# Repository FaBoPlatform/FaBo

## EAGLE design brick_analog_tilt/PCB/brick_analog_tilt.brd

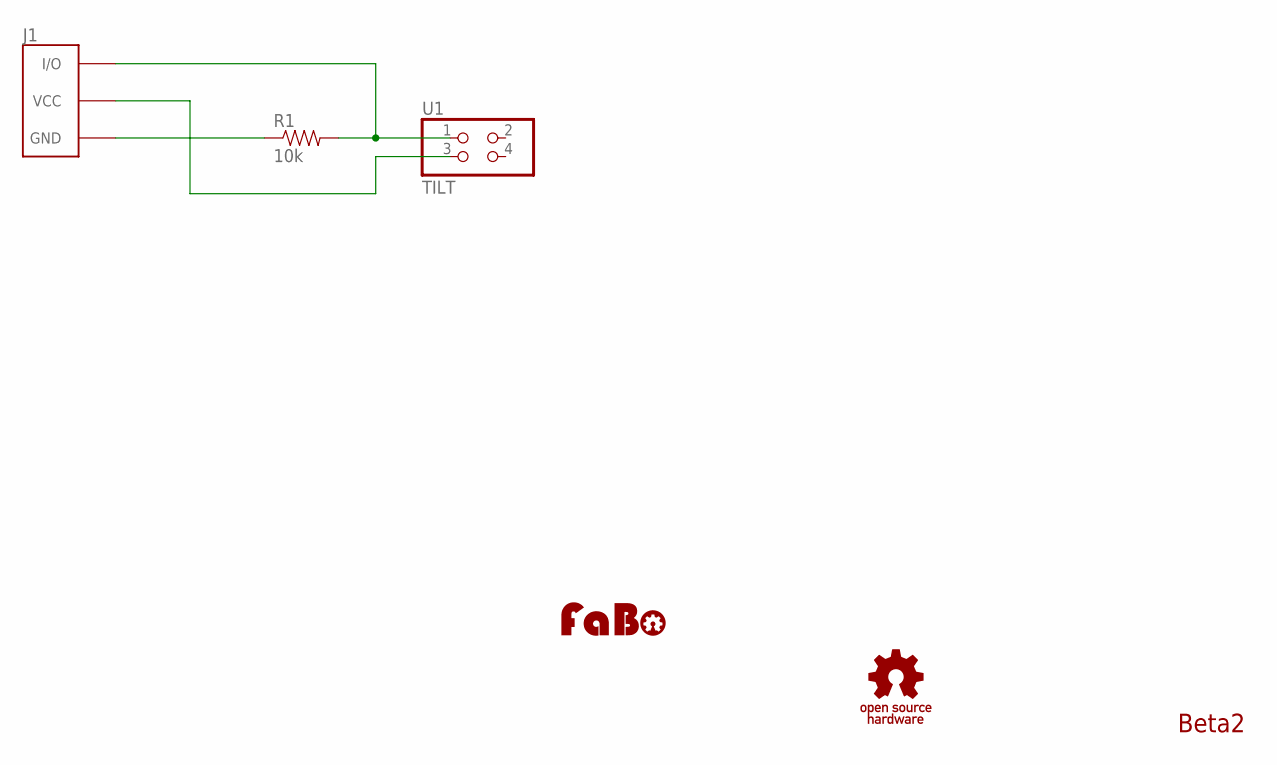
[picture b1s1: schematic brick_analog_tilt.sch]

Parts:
J1: BRICK_3PIN
R1: 10k; RES-AXL-REGULAR
U1: TILT; 2X02
U$2: LOGO_OSHW_T-M; LOGO_OSHW_T_M
U$3: LOGO_FABO-M; LOGO_FABO_M

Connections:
GND: J1.GND, R1.P$1 (1)
unnamed: J1.IN/OUT (I/O), R1.P$2 (2), U1.1
unnamed: J1.VCC, U1.3

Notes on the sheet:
Beta2

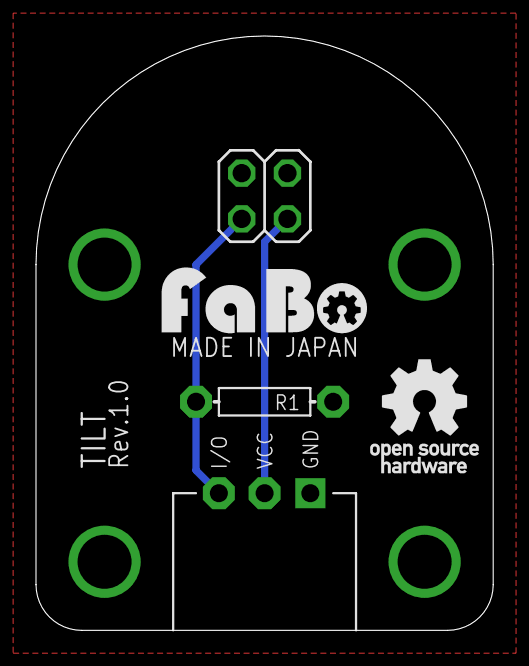
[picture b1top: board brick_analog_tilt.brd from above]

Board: 2 copper layers, 25.4 x 33.0 mm, 5 parts (0 on the bottom side), 3 nets.

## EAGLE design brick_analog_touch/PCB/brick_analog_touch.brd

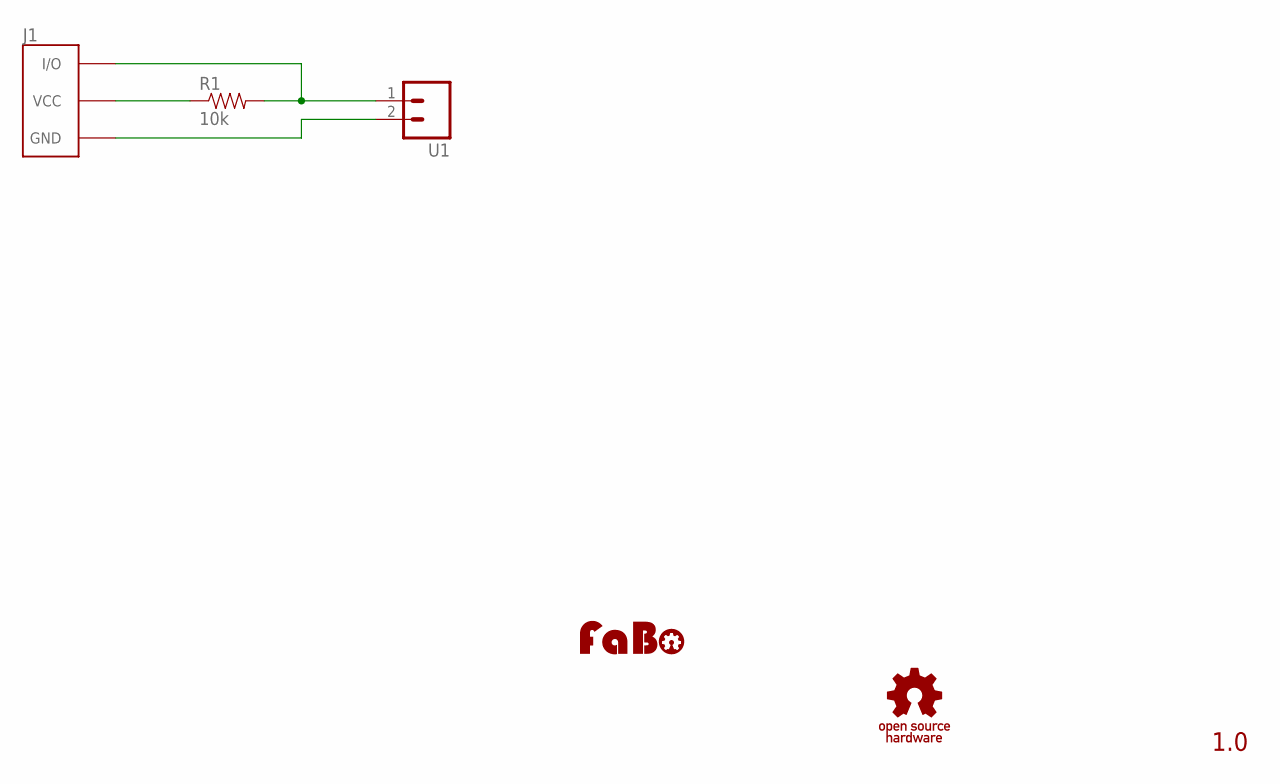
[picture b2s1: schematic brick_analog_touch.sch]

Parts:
J1: BRICK_3PIN_NORMAL; BRICK_3PIN
R1: 10k; RES-AXL-REGULAR
U1: M02LOCK; 1X02_LOCK
U$2: LOGO_OSHW_T-M; LOGO_OSHW_T_M
U$3: LOGO_FABO-M; LOGO_FABO_M

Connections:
GND: J1.GND, U1.2
unnamed: J1.IN/OUT (I/O), R1.P$2 (2), U1.1
unnamed: J1.VCC, R1.P$1 (1)

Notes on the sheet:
1.0

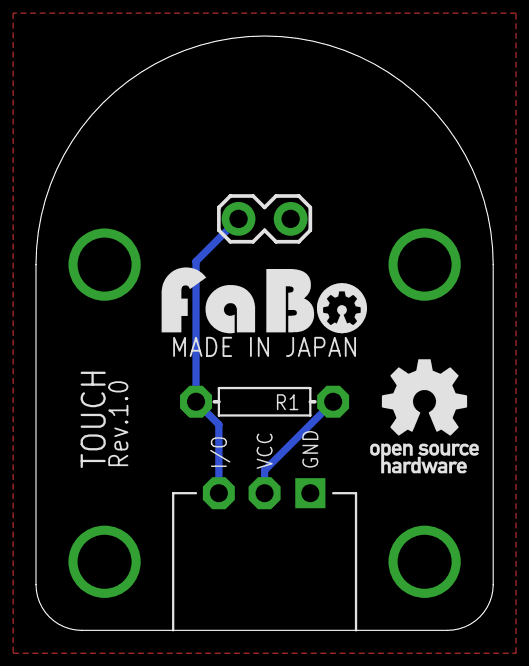
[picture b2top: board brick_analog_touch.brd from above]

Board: 2 copper layers, 25.4 x 33.0 mm, 5 parts (0 on the bottom side), 3 nets.

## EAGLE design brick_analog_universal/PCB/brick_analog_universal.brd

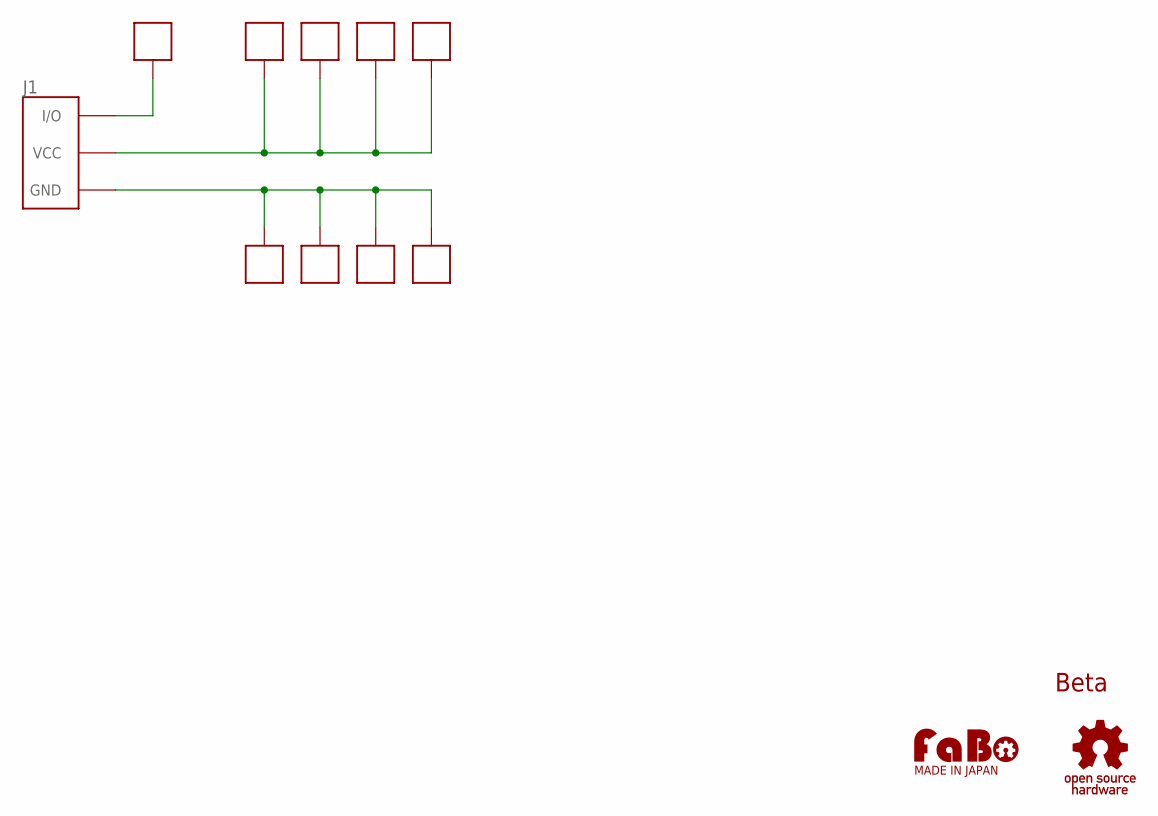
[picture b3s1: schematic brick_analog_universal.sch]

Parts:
J1: BRICK_3PIN_UNIVERSAL
U$1, U$3, U$4, U$5, U$6, U$7, U$8, U$9, U$10: PIN_FOR_UNIVERSAL
U$11: LOGO_FABO-BT; LOGO_FABO_M_BT
U$12: LOGO_OSHW-S_BOTTOM; LOGO_OSHW_S_BOTTOM

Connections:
GND: J1.GND, U$7.1, U$8.1, U$9.1, U$10.1
IO: J1.IN/OUT (I/O), U$1.1
VCC: J1.VCC, U$3.1, U$4.1, U$5.1, U$6.1

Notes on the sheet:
Beta

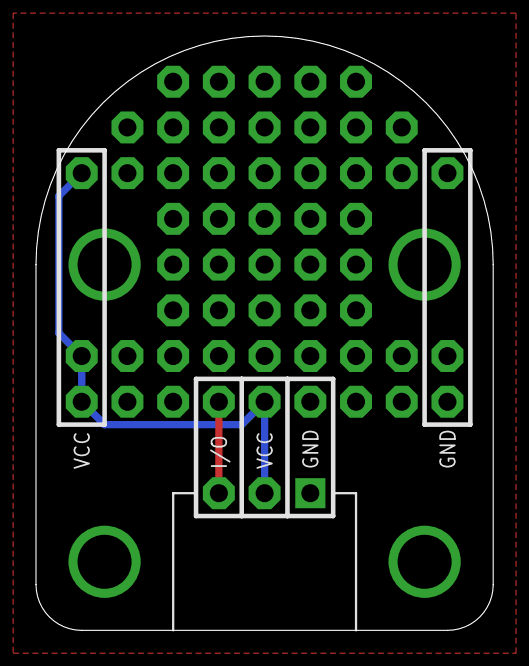
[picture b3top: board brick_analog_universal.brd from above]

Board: 2 copper layers, 25.4 x 33.0 mm, 12 parts (0 on the bottom side), 3 nets.

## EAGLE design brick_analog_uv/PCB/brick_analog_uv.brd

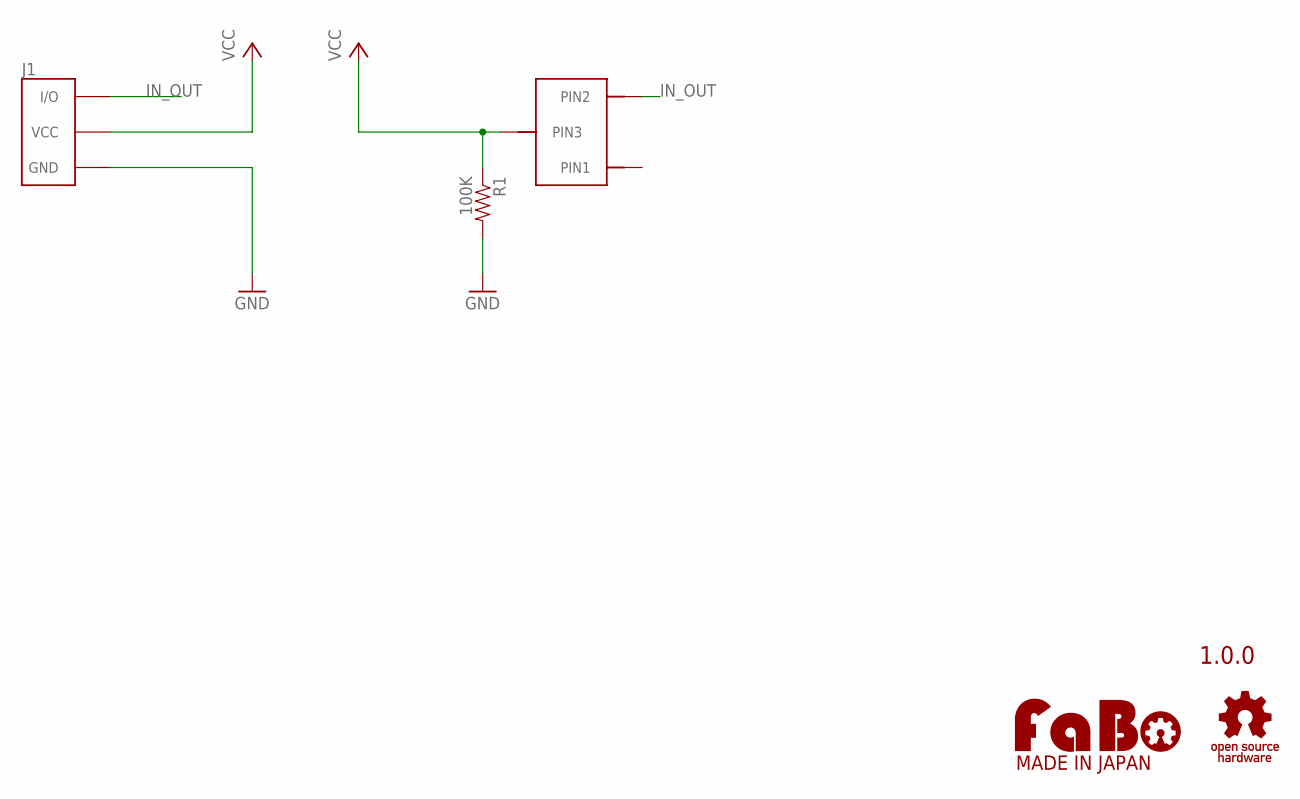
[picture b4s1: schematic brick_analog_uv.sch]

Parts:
J1: FABO_BRICK_3PIN
R1: 100K; 0603-RES
U1: HAMAMATSU-GAASP-G6262; GAASP-G6262
U$2: LOGO_OSHW-T_M; LOGO_OSHW_T_M
U$3: LOGO_FABO-M; LOGO_FABO_M

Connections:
GND: J1.GND, R1.2
IN_OUT: J1.IN/OUT (I/O), U1.2 (PIN2)
VCC: J1.VCC, R1.1, U1.3 (PIN3)

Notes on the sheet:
1.0.0

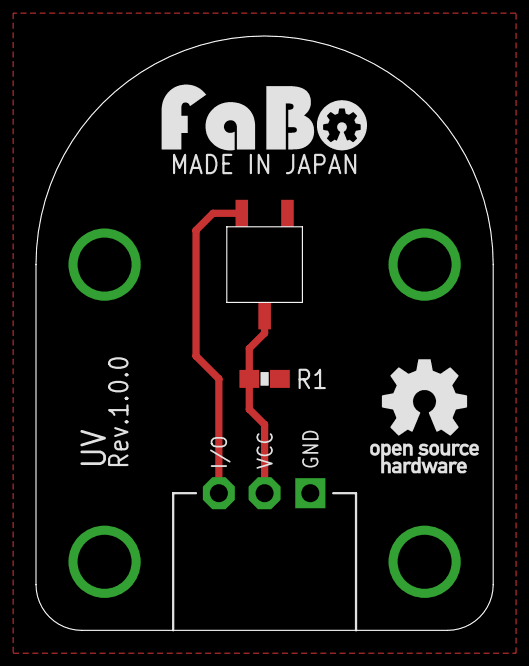
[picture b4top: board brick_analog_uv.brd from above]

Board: 2 copper layers, 25.4 x 33.0 mm, 5 parts (0 on the bottom side), 3 nets.

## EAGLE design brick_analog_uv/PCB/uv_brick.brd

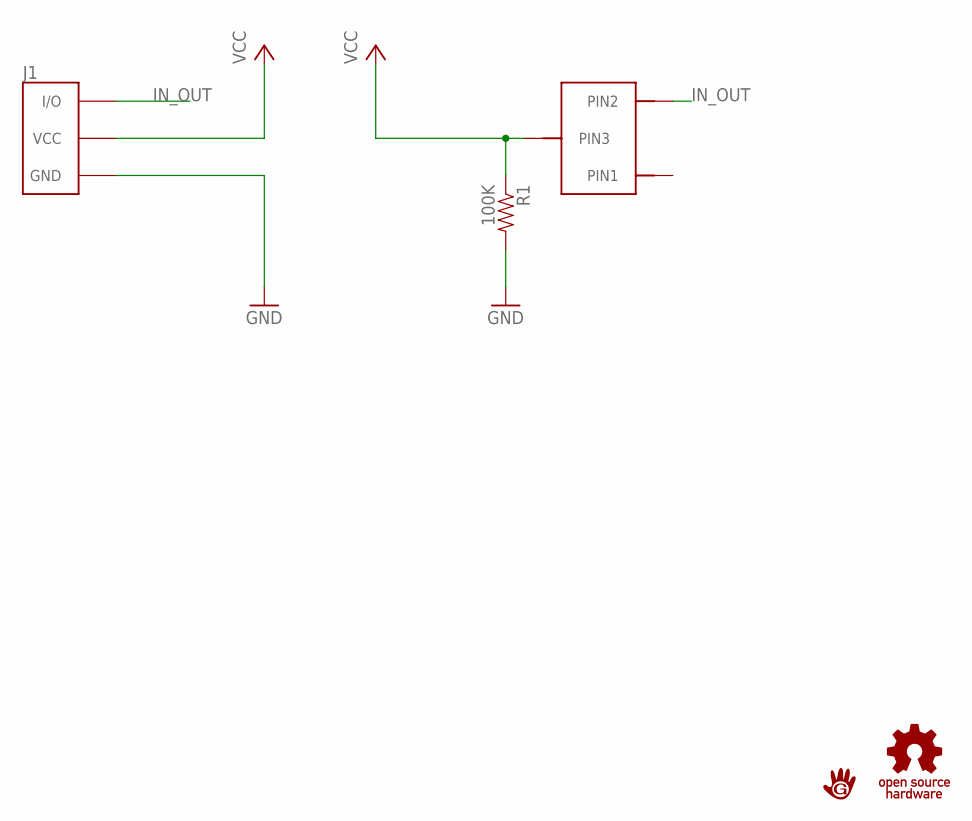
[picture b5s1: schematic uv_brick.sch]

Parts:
J1: BRICK_3PIN
R1: 100K; 0603-RES
U$1: GAASP-G6262
U$3: LOGO_GCLUE-M; LOGO_GCLUE_M
U$4: LOGO_OSHW_T-M; LOGO_OSHW_T_M

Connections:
GND: J1.GND, R1.2
IN_OUT: J1.IN/OUT (I/O), U$1.2 (PIN2)
VCC: J1.VCC, R1.1, U$1.3 (PIN3)

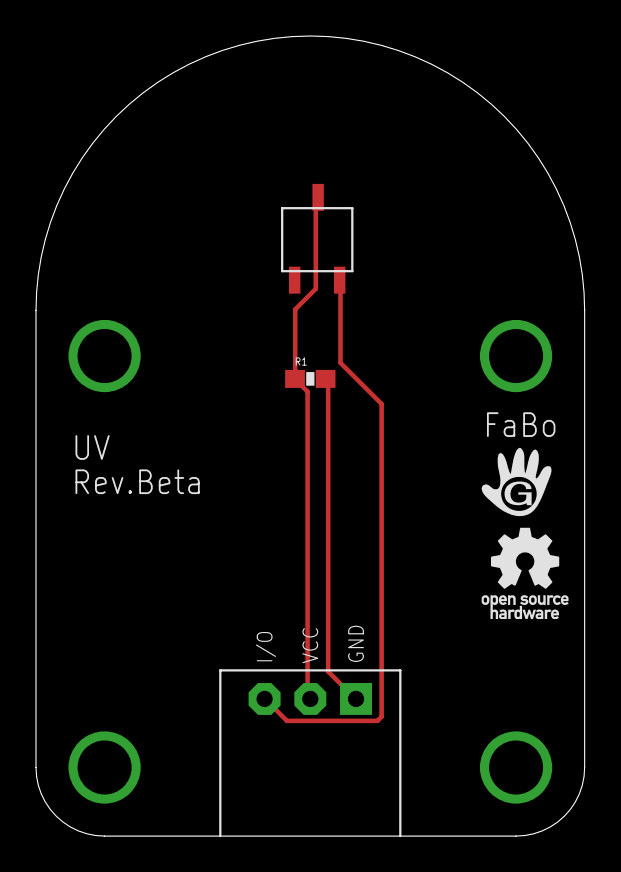
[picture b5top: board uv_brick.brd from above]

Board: 2 copper layers, 30.5 x 44.5 mm, 5 parts (0 on the bottom side), 3 nets.

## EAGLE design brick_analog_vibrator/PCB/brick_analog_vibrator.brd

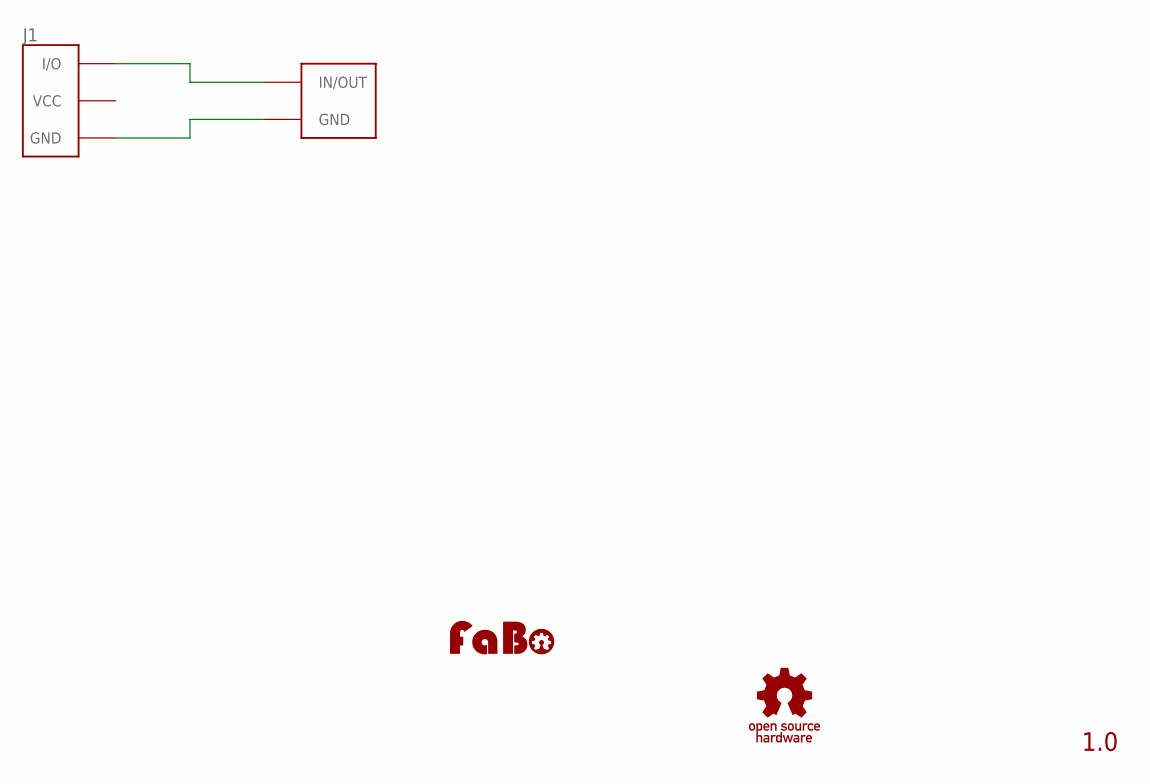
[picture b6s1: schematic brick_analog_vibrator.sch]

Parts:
J1: BRICK_3PIN_NORMAL; BRICK_3PIN
U1: LA3R5-480H1-PTH; LA3R5-480AH1_PTH
U$1: LOGO_FABO-M; LOGO_FABO_M
U$5: LOGO_OSHW_T-M; LOGO_OSHW_T_M

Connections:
GND: J1.GND, U1.P$2 (GND)
unnamed: J1.IN/OUT (I/O), U1.P$1 (IN/OUT)

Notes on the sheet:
1.0

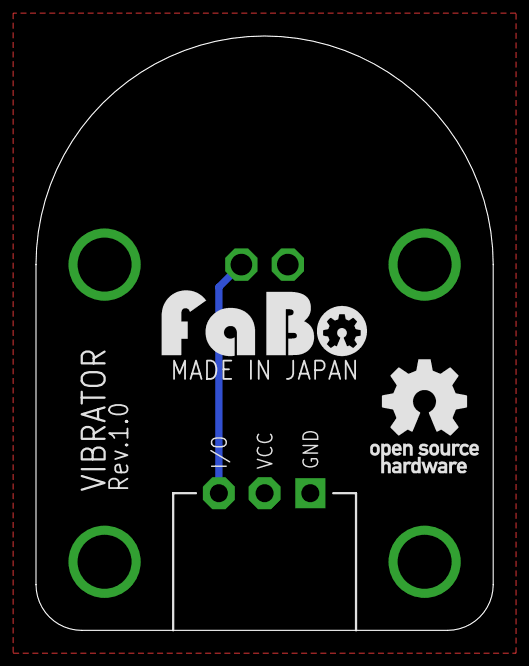
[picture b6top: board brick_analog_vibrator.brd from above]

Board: 2 copper layers, 25.4 x 33.0 mm, 4 parts (0 on the bottom side), 2 nets.

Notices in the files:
parts and their libraries:
SparkFun: Licensing: CC v3.0 Share-Alike You are welcome to use this library for commercial purposes.
FaBo-etc: Released under the Creative Commons Attribution-ShareAlike 4.0 License
https://creativecommons.org/licenses/by-sa/4.0
FaBo-etc: Released under the Creative Commons
